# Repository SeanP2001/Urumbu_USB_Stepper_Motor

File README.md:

# Urumbu USB Stepper Motor

**This Project follows on from the work of Professor Neil Gershenfeld, Quentin Bolsee and Rob Hart at MIT. [Here](https://gitlab.cba.mit.edu/neilg/urumbu) is the original repository.**

## Table of Contents <!-- omit from toc -->

- [Introduction](#introduction)
- [Brief](#brief)
- [Design Aims](#design-aims)
- [PCB Design](#pcb-design)
- [Manufacturing](#manufacturing)
- [Programming](#programming)
  - [Flashing SAMD11 Firmware](#flashing-samd11-firmware)
  - [Adding the Arduino IDE Board Manager](#adding-the-arduino-ide-board-manager)
  - [The Arduino Code](#the-arduino-code)
  - [The Test Code](#the-test-code)
- [Motor Module Characteristics](#motor-module-characteristics)
  - [Current Draw](#current-draw)
  - [Motor Speed](#motor-speed)
  - [Motor Torque](#motor-torque)
- [Using the Module](#using-the-module)
- [Conclusion](#conclusion)
- [Further Work](#further-work)

## Introduction

In the final year of my Bachelors degree I completed a dissertation. This repository is a summary of that work. Included in the repository is all of the information and files to reproduce and use the modules which I designed.

Bangor FabLAB needed to develop methods to teach the Fab Academy curriculum. The curriculum includes two weeks of making machines that move. Students have a very limited time to complete these projects and so they needed a flexible framework which could be used to rapidly prototype motion systems.

Traditional motion systems have all of the components plugged into the controller board. This board has firmware code to control all of the components. While prototyping, it is common to want to add parts like extra motors or switches. With this approach, the controller board must be re-designed, manufactured and programmed. This is time-consuming, creates waste, breaks the creative flow, and requires substantial skills. Students only have one week to do their projects, and this approach is not suitable.

Professor Neil Gershenfeld and his colleagues Quentin Bolsee and Rob Hart have developed a modular solution to this problem called [Urumbu](https://gitlab.cba.mit.edu/neilg/urumbu). These modules are designed to plug into a computer via a USB port. The modules move in response to serial communications from the connected computer. To add more motors to an Urumbu-based machine, the user simply plugs another motor module into the PC and adds it to their code. This is much quicker and does not break the creative flow.

## Brief

I was tasked with equipping the FabLAB to teach the machine building exercises. This involved...
- Adapting the Urumbu design to meet our requirements.
- Manufacturing a set of modules.
- Testing and documenting the module characteristics to understand their capabilities.
- Demonstrating their use through building a motion system. 

## Design Aims

The original design used a DRV8428 motor driver. This motor driver causes the motor to generate noise. This driver is also surface-mount and so if the driver were to fail mid-project, it would be difficult and time-consuning to replace. 

With these issues in mind, I aimed to design a module with the following characteristics:
- Use a silent, user replaceable stepper motor driver (TMC2208, StepStick socketed package).
- Able to be mounted to the back of a NEMA 14 motor.
- Able to be manufactured in the FabLAB using their isolation milling process with FR1 board.

## PCB Design

After three breadboard prototypes and six circuit board revisions I arrived at this design.

The top section is the power section which takes the five volts from the USB connection and steps it down to a stable 3.3 volts for the microcontroller. The main use for the SAMD microcontroller is to interpret the information from the USB data lines and send the correct direction and step signals to the motor driver. The motor driver connects to the four motor pins and pulses them in sequence to advance the motor whenever it receives a step signal.

## Manufacturing

Images of the PCB were exported from KiCAD. Using [modsproject](https://modsproject.org/), these images were converted into toolpaths and saved in `./PCB_Design/Toolpaths`. Using the Roland SRM-20 CNC mill with a 0.4mm end mill, the traces were isolation milled out of a copper-clad FR1 board. A 0.7mm end mill was then used to drill the holes and cut the board outline. The components were soldered by hand using a soldering iron, as this is the best method for FR1 boards.

|   |  |
| --- | --- |

## Programming

### Flashing SAMD11 Firmware

The ["ArduinoCore"](https://github.com/mattairtech/ArduinoCore-samd/blob/master/bootloaders/zero/binaries/sam_ba_Generic_D11C14A_SAMD11C14A.bin) firmware was loaded on to the SAMD11 microcontroller to allow it to be programmed via USB. To do this, I used an Atmel-ICE programmer with the "mini-squid" cable and connected it to the microcontroller in the following way:

| SAM Programming Header Pin Number | Function | SAMD11C Pin Number |
| --- | --- | --- |
| 1 | VREF | 12 |
| 2 | DIO | 8 |
| 3 | GND | 11 |
| 4 | CLK | 7 |
| 5 | GND | 11 |
| 6 | Not Connected |   |
| 7 | Not Connected |   |
| 8 | Not Connected |   |
| 9 | GND | 11 |
| 10 |RST | 6 |

I used a crocodile clip to connect the ground connections to the ground plane. The voltage reference pin was connected via a test clip to the 3V jumper wire on the circuit board. The other connections were connected to a pogo-pin board which was held against the programming pads when the board was being programmed. The board recieved power through the USB connection. 

Atmel Studio was used to load the firmware onto the microcontroller. While holding the pogo pins to the pads, I selected `Device Programming > Apply` and the device was successfully connected to. On the "Memories" tab I selected the [firmware file](https://github.com/mattairtech/ArduinoCore-samd/blob/master/bootloaders/zero/binaries/sam_ba_Generic_D11C14A_SAMD11C14A.bin) and clicked "Apply" to write the firmware to the microcontroller.

### Adding the Arduino IDE Board Manager

The [Fab SAM board manager](https://raw.githubusercontent.com/qbolsee/ArduinoCore-fab-sam/master/json/package_Fab_SAM_index.json) was added to the Arduino IDE, following the [MIT guide](https://mtm.cba.mit.edu/2021/2021-10_microcontroller-primer/fab-arduino/). This allowed the Arduino IDE to be used to program the SAMD11C on the PCB.

### The Arduino Code

The Arduino code running on the Urumbu modules was very heavily inspired by the [original “serialstep” code](https://gitlab.cba.mit.edu/neilg/urumbu/-/tree/master/serialstep/serialstep.ino) used at MIT. The premise of the code is to continuously check whether any serial data has been sent via the USB connection. If the received data is an ’f’, the stepper motor will step clockwise (forwards). If the received data is an ’r’, the stepper motor will step anti-clockwise (reverse).

### The Test Code

The `./Test_Code/SerialStepControllerTest.py` code sends 'f' and 'r' characters via USB to the motor module to turn the shaft one rotation clockwise and then anti-clockwise repeatedly.

The `./Test_Code/SerialStepKeyboardControllerTest.py` code sends 'f' and 'r' characters via USB to the motor module to turn the shaft in response to the user pressing the arrow keys on the PC.

## Motor Module Characteristics

These documented characteristics should help anybody aiming to use these modules by giving them the information to assess whether these modules are capable of fulfilling their requirements.

### Current Draw

| Motor State | Lowest Current Draw (A) | Highest Current Draw (A) | Average Current Draw (A) | 
| --- | --- | --- | --- | 
| Idle | 0.13 | 0.19 | 0.16 |
| Moving | 0.31 | 0.37 | 0.34 |
| Moving with 5Ncm Load | 0.31 | 0.37 | 0.34 |

### Motor Speed

The maximum speed of the motor is approximately 2.64 revolutions per second or 158.5 revolutions per minute.

### Motor Torque

The motor was able to lift a mass of 100g at a distance of 6.8cm from the motor shaft. This gives a torque figure of 6.67Ncm.

## Using the Module

I then went on to demonstrate the use of these modules and test that they functioned as expected. To do this I designed, manufactured and programmed a crane motion system. [Here](https://github.com/SeanP2001/Urumbu_Crane) is the repository for that project.

|   |  |
| --- | --- |

## Conclusion

In conclusion, I designed a set of stepper motor Urumbu modules to use a silent, user-replaceable motor driver. A set of modules was manufactured using standard FabLAB tools and parts. The current draw, speed and torque of the motor modules were tested and documented for future students to reference. I also designed and built a motion system to demonstrate the use of these modules. Overall this project was a success. The modules met the brief and will soon be used by Fab Academy students.

## Further Work

There are a few aspects of this project which could be furnter developed:
- Design more modules
  - Button Interface (Controller)
  - Limit Switch
  - LCD
- Write a Python Library to simplify the controller code that students need to write. They could use simple functions to control the modules, rather than dealing with the specifics of the serial communications and distance calculations.

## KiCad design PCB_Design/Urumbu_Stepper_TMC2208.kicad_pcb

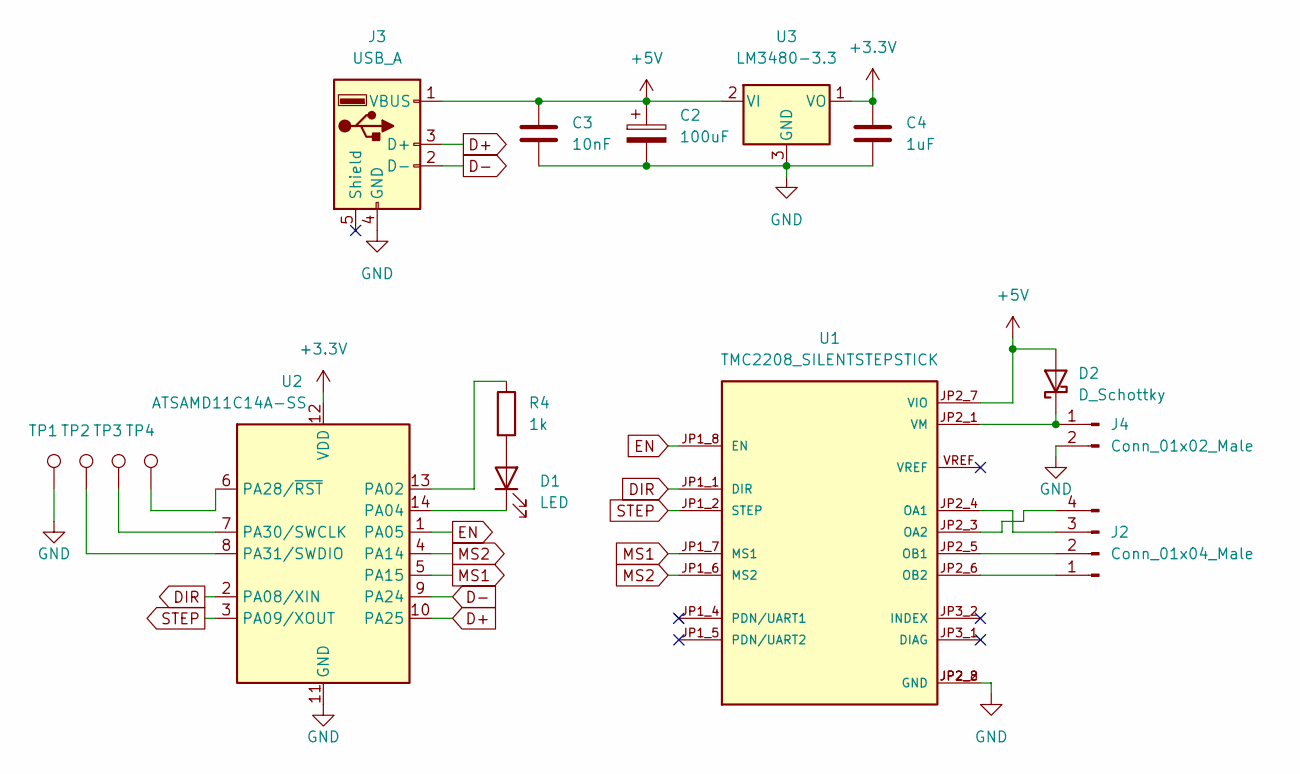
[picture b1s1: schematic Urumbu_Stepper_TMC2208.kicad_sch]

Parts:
C2: 100uF; CP_Radial_D6.3mm_P2.50mm
C3: 10nF; C_1206_3216Metric_Pad1.33x1.80mm_HandSolder
C4: 1uF; C_1206_3216Metric_Pad1.33x1.80mm_HandSolder
D1: LED; LED_1210_3225Metric_Pad1.42x2.65mm_HandSolder
D2: D_Schottky; D_SOD-123
J2: Conn_01x04_Male; PinHeader_1x04_P2.54mm_Vertical
J3: USB_A; Conn_USB_A_Plain
J4: Conn_01x02_Male; PinHeader_1x02_P2.54mm_Vertical
R4: 1k; R_1206
TP1, TP2, TP3, TP4: TestPoint; TestPoint_Pad_D2.0mm
U1: TMC2208_SILENTSTEPSTICK; TMC2208
U2: ATSAMD11C14A-SS; SOIC-14_3.9x8.7mm_P1.27mm
U3: LM3480-3.3; SOT-23_N_Package

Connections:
+3.3V: C4.1, U2.12 (VDD), U3.1 (VO)
+5V: C2.1, C3.1, D2.2 (A), J3.1 (VBUS), U1.JP2_7 (VIO), U3.2 (VI)
D+: J3.3 (D+), U2.10 (PA25)
D-: J3.2 (D-), U2.9 (PA24)
DIR: U1.JP1_1 (DIR), U2.2 (PA08/XIN)
EN: U1.JP1_8 (EN), U2.1 (PA05)
GND: C2.2, C3.2, C4.2, J3.4 (GND), J4.2, TP1.1, U1.JP2_2 (GND), U1.JP2_8 (GND), U2.11 (GND), U3.3 (GND)
MS1: U1.JP1_7 (MS1), U2.5 (PA15)
MS2: U1.JP1_6 (MS2), U2.4 (PA14)
unnamed: D1.1 (K), U2.14 (PA04)
unnamed: D1.2 (A), R4.2
unnamed: D2.1 (K), J4.1, U1.JP2_1 (VM)
unnamed: J2.1, U1.JP2_6 (OB2)
unnamed: J2.2, U1.JP2_5 (OB1)
unnamed: J2.3, U1.JP2_4 (OA1)
unnamed: J2.4, U1.JP2_3 (OA2)
unnamed: R4.1, U2.13 (PA02)
unnamed: TP4.1, U2.6 (PA28/~RST)
unnamed: TP3.1, U2.7 (PA30/SWCLK)
unnamed: TP2.1, U2.8 (PA31/SWDIO)
STEP: U1.JP1_2 (STEP), U2.3 (PA09/XOUT)

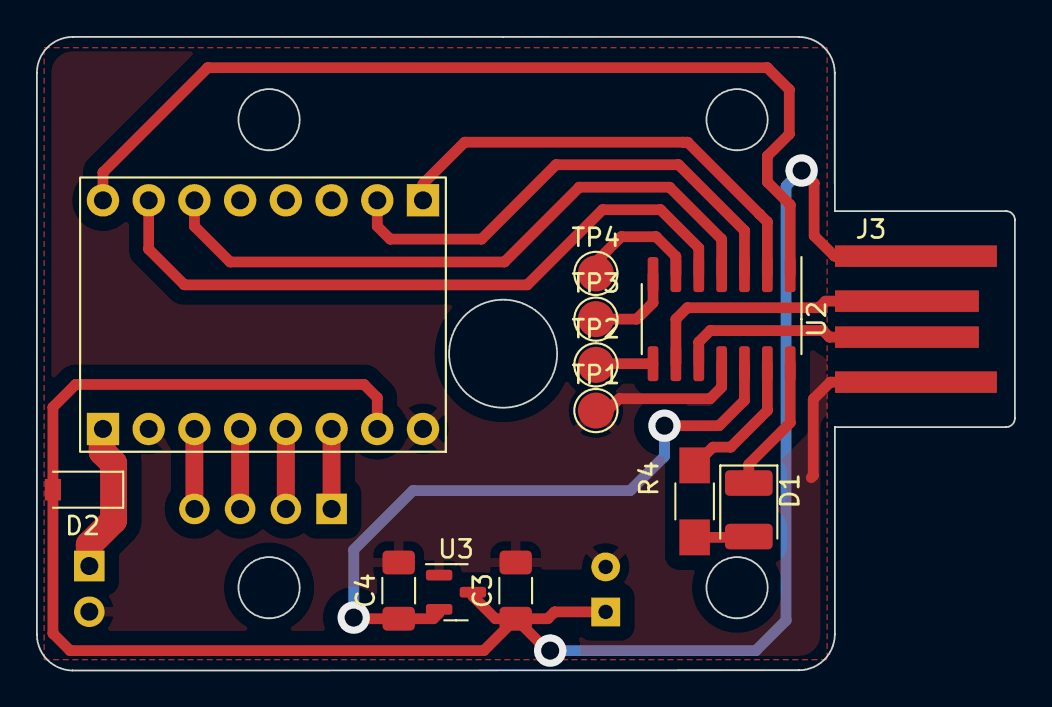
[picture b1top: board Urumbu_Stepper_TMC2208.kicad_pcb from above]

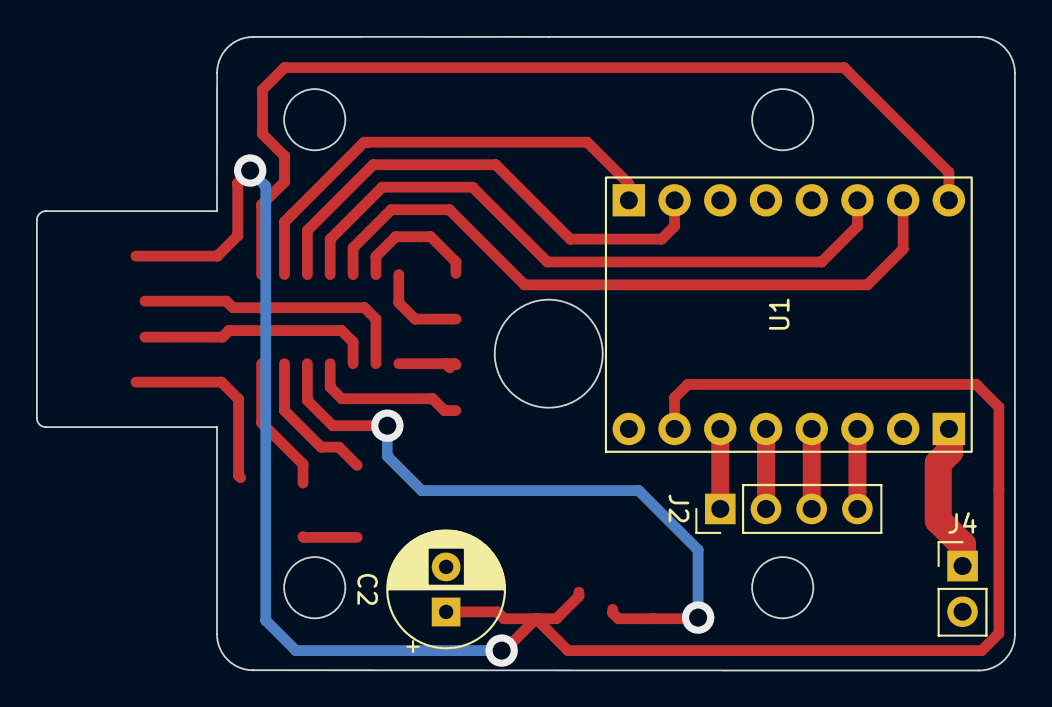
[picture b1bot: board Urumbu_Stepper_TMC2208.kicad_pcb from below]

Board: 2 copper layers, 54.3 x 35.2 mm, 16 parts (4 on the bottom side), 21 nets.

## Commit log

2023-09-24 V0.1.0 Started Documenting Project
2023-09-25 V1.0.0 Finished Writing README.md
2023-09-27 V1.0.1 Added Link to Crane Repo
